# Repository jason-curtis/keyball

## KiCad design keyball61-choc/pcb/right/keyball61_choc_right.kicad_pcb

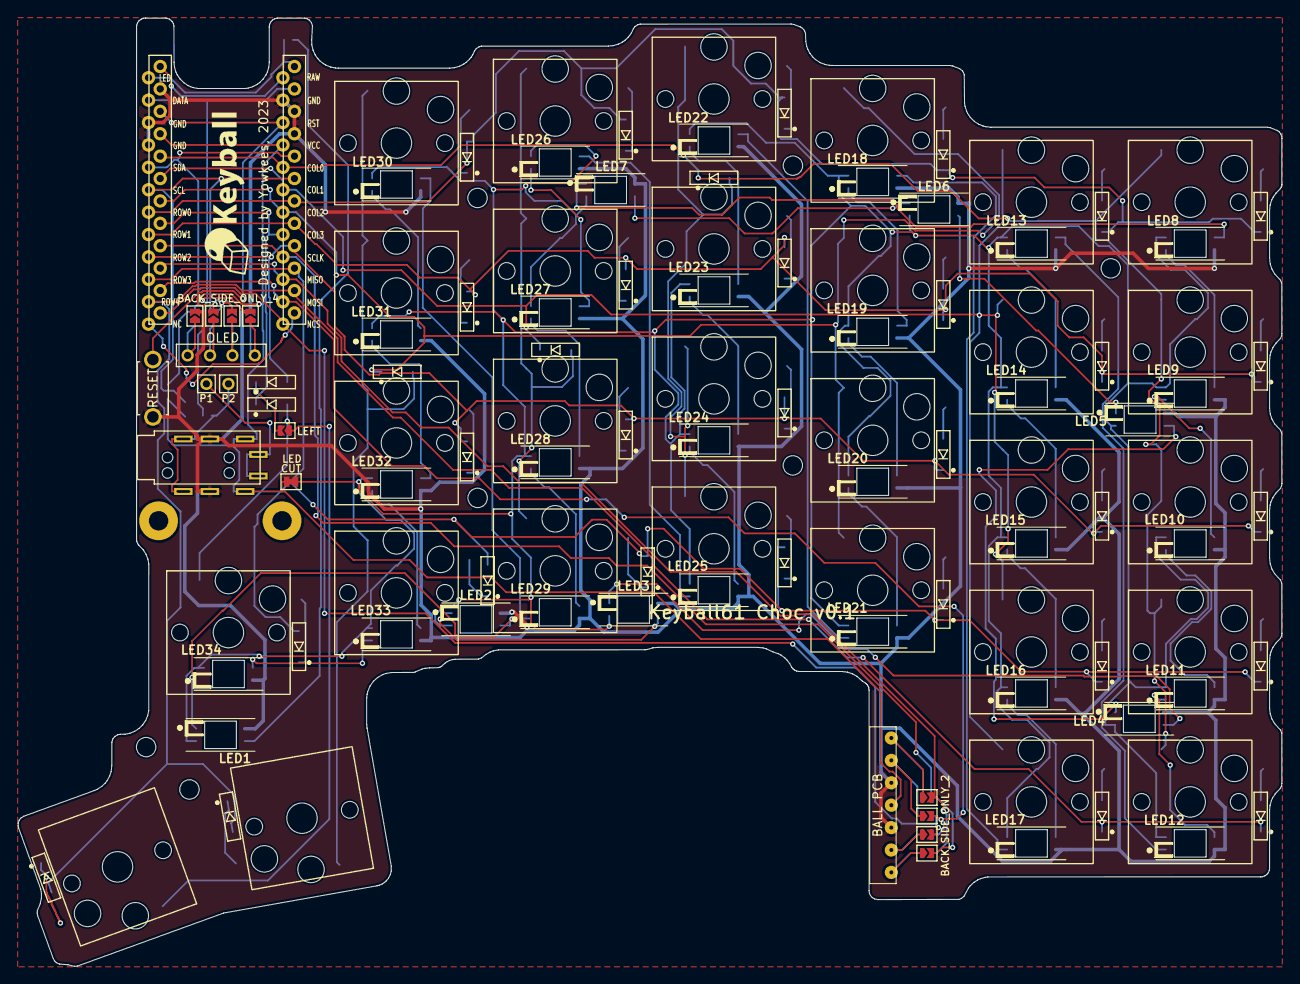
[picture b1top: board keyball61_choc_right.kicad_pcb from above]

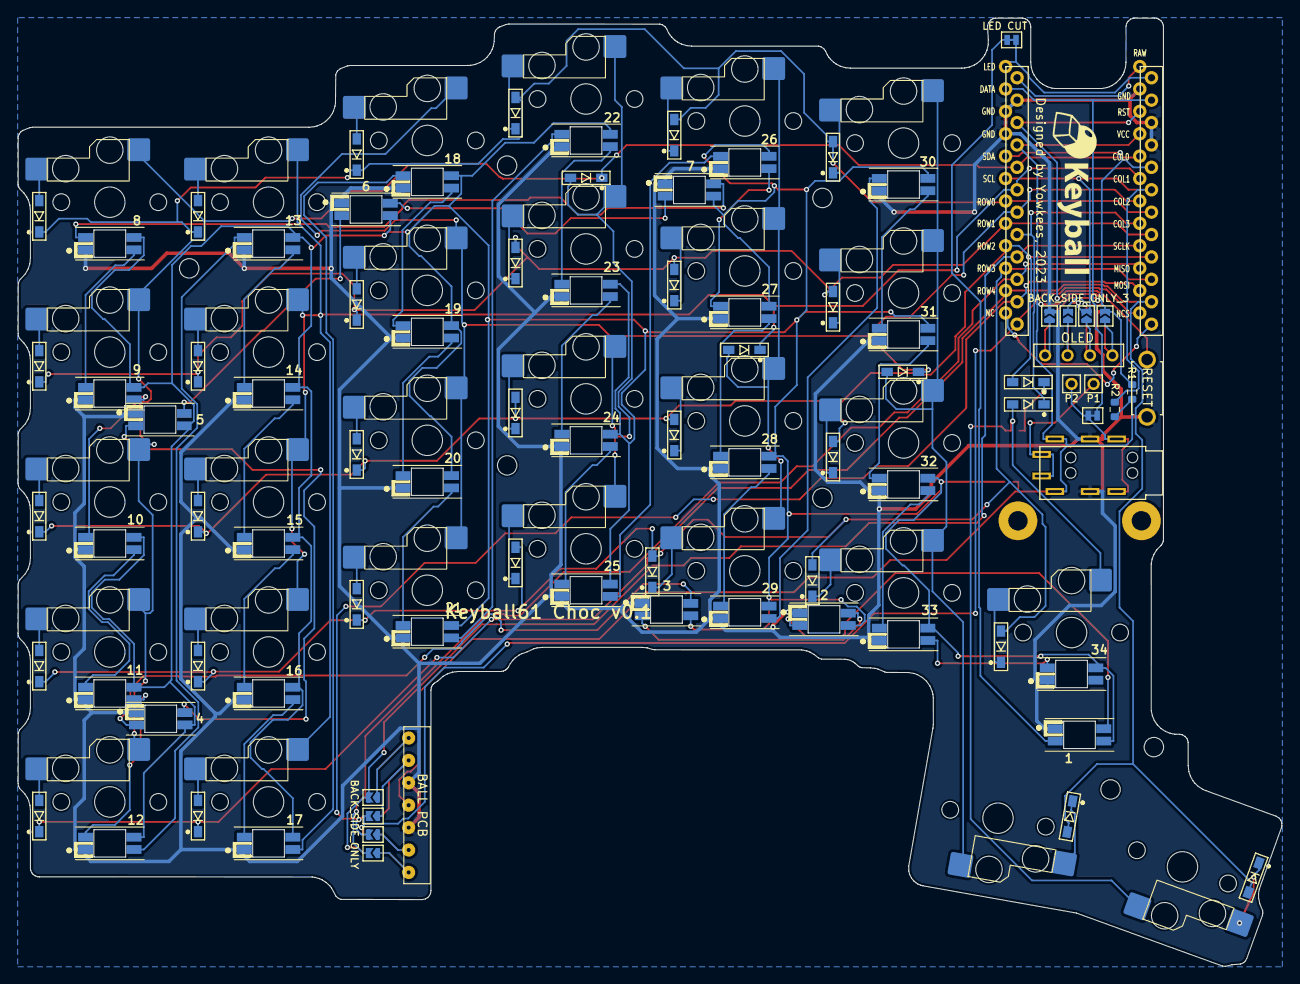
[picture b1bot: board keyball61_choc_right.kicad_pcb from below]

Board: 2 copper layers, 143.3 x 107.5 mm, 137 parts (13 on the bottom side), 99 nets.

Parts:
BACK_SIDE_ONLY: Device_Jumper_NO_Small; Jumper_NEW
BACK_SIDE_ONLY_2, BACK_SIDE_ONLY_3, BACK_SIDE_ONLY_4: Device_Jumper_NO_Small; Jumper_NEW
D1, D2, D3, D4, D5, D6, D7, D8, D9, D10, D11, D12, D13, D14, D15, D16, D17, D18, D19, D20, D21, D22, D23, D24, D25, D26, D27, D28, D29, D30, D31, D32, D33, D34: D; D3_SMD_v2_BOTH
GXXX: LOGO; keyball_logo700
GXXX_2: LOGO; keyball_logo700
J1: OLED
J2: BALL_PCB; Mac8_L_7pin_contact_NEW2023
J3, J4: Conn_01x01-Connector_Generic; MountingHole_2.2mm_M2_Pad
J13: TRS_JACK; TRRS_JACK_MJ4PP9
JP1, JP2, JP3, JP4, JP7, JP8, JP10, JP11, JP12, JP13, JP15, JP16: Device_Jumper_NO_Small; Jumper_NEW
JP18: Device_Jumper; JP025
JP20: LED CUT; JP025
LED: CUT; JP06
LED1, LED2, LED3, LED4, LED5, LED6, LED7: YS-SK6812MINI-E; YS-SK6812MINI-Keyball-BL
LED8, LED9, LED10, LED11, LED12, LED13, LED14, LED15, LED16, LED17, LED18, LED19, LED20, LED21, LED22, LED23, LED24, LED25, LED26, LED27, LED28, LED29, LED30, LED31, LED32, LED33, LED34: YS-SK6812MINI-E; YS-SK6812MINI-Keyball-TL
LEFT: Device_Jumper_NO_Small; Jumper_NEW
MH5, MH6, MH7, MH8, MH9, MH11, MH12: M2; MountingHole_2.2mm_M2
P1, P2: I2C; 1pin_conn
R1, R2: PULL_UP; R_0603_1608Metric
SW1, SW2, SW3, SW4, SW5, SW6, SW7, SW8, SW9, SW10, SW11, SW12, SW13, SW14, SW15, SW16, SW17, SW18, SW19, SW20, SW21, SW22, SW23, SW24, SW25, SW26, SW27, SW28, SW29: Choc_V1; Choc_V1_Hotswap
SW30: RESET_SW; ResetSW
U1: ProMicro-kbd; ProMicro_v2_for61

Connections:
COL0: D31.1, SW1.1, SW7.1, SW13.1, SW19.1, SW26.1, U1.20
COL1: D32.1, SW2.1, SW8.1, SW14.1, SW20.1, SW27.1, U1.19
COL2: D33.1, SW3.1, SW9.1, SW15.1, SW21.1, U1.18
COL3: D34.1, U1.17
DATA: JP18.2, U1.2
GND: BACK_SIDE_ONLY_3.2, J2.3, J2.5, J13.C, JP2.2, LED1.3, LED2.3, LED3.3, LED4.3, LED5.3, LED6.3, LED7.3, LED8.3, LED9.3, LED10.3, LED11.3, LED12.3, LED13.3, LED14.3, LED15.3, LED16.3, LED17.3, LED18.3, LED19.3, LED20.3, LED21.3, LED22.3, LED23.3, LED24.3, LED25.3, LED26.3, LED27.3, LED28.3, LED29.3, LED30.3, LED31.3, LED32.3, LED33.3, LED34.3, SW30.2, U1.3, U1.4, U1.23
LED: JP20.1, U1.1
MISO: JP1.2, JP16.2, U1.15
MOSI: BACK_SIDE_ONLY.2, JP3.2, U1.14
NCS: BACK_SIDE_ONLY_2.2, JP12.2, U1.13
unnamed: D1.2, SW1.2
unnamed: D2.2, SW2.2
unnamed: D3.2, SW3.2
unnamed: D4.1, SW4.2
unnamed: D5.1, SW5.2
unnamed: D6.1, SW6.2
unnamed: D7.2, SW7.2
unnamed: D8.2, SW8.2
unnamed: D9.2, SW9.2
unnamed: D10.1, SW10.2
unnamed: D11.1, SW11.2
unnamed: D12.1, SW12.2
unnamed: D13.2, SW13.2
unnamed: D14.2, SW14.2
unnamed: D15.2, SW15.2
unnamed: D16.1, SW16.2
unnamed: D17.1, SW17.2
unnamed: D18.1, SW18.2
unnamed: D19.2, SW19.2
unnamed: D20.2, SW20.2
unnamed: D21.2, SW21.2
unnamed: D22.1, SW22.2
unnamed: D23.1, SW23.2
unnamed: D24.1, SW24.2
unnamed: D25.1, SW25.2
unnamed: D26.2, SW26.2
unnamed: D27.2, SW27.2
unnamed: D28.1, SW28.2
unnamed: D29.1, SW29.2
unnamed: D30.1, LEFT.2
unnamed: D31.2, SW4.1, SW10.1, SW16.1, SW22.1
unnamed: D32.2, SW5.1, SW11.1, SW17.1, SW23.1
unnamed: D33.2, SW6.1, SW12.1, SW18.1, SW24.1, SW28.1
unnamed: D34.2, LEFT.1, SW25.1, SW29.1
unnamed: J1.1, JP2.1, JP11.1
unnamed: J1.2, JP4.1, JP13.1
unnamed: BACK_SIDE_ONLY_4.1, J1.3, JP15.1
unnamed: BACK_SIDE_ONLY_3.1, J1.4, JP8.1
unnamed: J2.1, JP1.1, JP10.1
unnamed: J2.2, JP3.1, JP12.1
unnamed: BACK_SIDE_ONLY.1, BACK_SIDE_ONLY_2.1, J2.6
unnamed: J2.7, JP7.1, JP16.1
unnamed: J13.A, P1.1
unnamed: J13.B, JP18.1, P2.1
unnamed: LED.1, LED1.1, LED2.1, LED3.1, LED4.1, LED5.1, LED6.1, LED7.1, LED8.1, LED9.1, LED10.1, LED11.1, LED12.1, LED13.1, LED14.1, LED15.1, LED16.1, LED17.1, LED18.1, LED19.1, LED20.1, LED21.1, LED22.1, LED23.1, LED24.1, LED25.1, LED26.1, LED27.1, LED28.1, LED29.1, LED30.1, LED31.1, LED32.1, LED33.1, LED34.1
unnamed: JP20.2, LED1.4
unnamed: LED1.2, LED2.4
unnamed: LED2.2, LED3.4
unnamed: LED3.2, LED4.4
unnamed: LED4.2, LED5.4
unnamed: LED5.2, LED6.4
unnamed: LED6.2, LED7.4
unnamed: LED7.2, LED8.4
unnamed: LED8.2, LED9.4
unnamed: LED10.2, LED11.4
unnamed: LED9.2, LED10.4
unnamed: LED11.2, LED12.4
unnamed: LED12.2, LED13.4
unnamed: LED13.2, LED14.4
unnamed: LED14.2, LED15.4
unnamed: LED15.2, LED16.4
unnamed: LED16.2, LED17.4
unnamed: LED17.2, LED18.4
unnamed: LED18.2, LED19.4
unnamed: LED19.2, LED20.4
unnamed: LED20.2, LED21.4
unnamed: LED21.2, LED22.4
unnamed: LED22.2, LED23.4
unnamed: LED23.2, LED24.4
unnamed: LED24.2, LED25.4
unnamed: LED25.2, LED26.4
unnamed: LED26.2, LED27.4
unnamed: LED27.2, LED28.4
unnamed: LED28.2, LED29.4
unnamed: LED29.2, LED30.4
unnamed: LED30.2, LED31.4
unnamed: LED31.2, LED32.4
unnamed: LED32.2, LED33.4
unnamed: LED33.2, LED34.4
RESET: SW30.1, U1.22
ROW0: D1.1, D2.1, D3.1, D4.2, D5.2, D6.2, U1.7
ROW1: D7.1, D8.1, D9.1, D10.2, D11.2, D12.2, U1.8
ROW2: D13.1, D14.1, D15.1, D16.2, D17.2, D18.2, D30.2, U1.9
ROW3: D19.1, D20.1, D21.1, D22.2, D23.2, D24.2, D25.2, U1.10
ROW4: D26.1, D27.1, D28.2, D29.2, U1.11
SCL: BACK_SIDE_ONLY_4.2, JP13.2, R2.2, U1.6
SCLK: JP7.2, JP10.2, U1.16
SDA: JP8.2, JP11.2, R1.2, U1.5
VCC: J2.4, J13.D, JP4.2, JP15.2, LED.2, R1.1, R2.1, U1.21
